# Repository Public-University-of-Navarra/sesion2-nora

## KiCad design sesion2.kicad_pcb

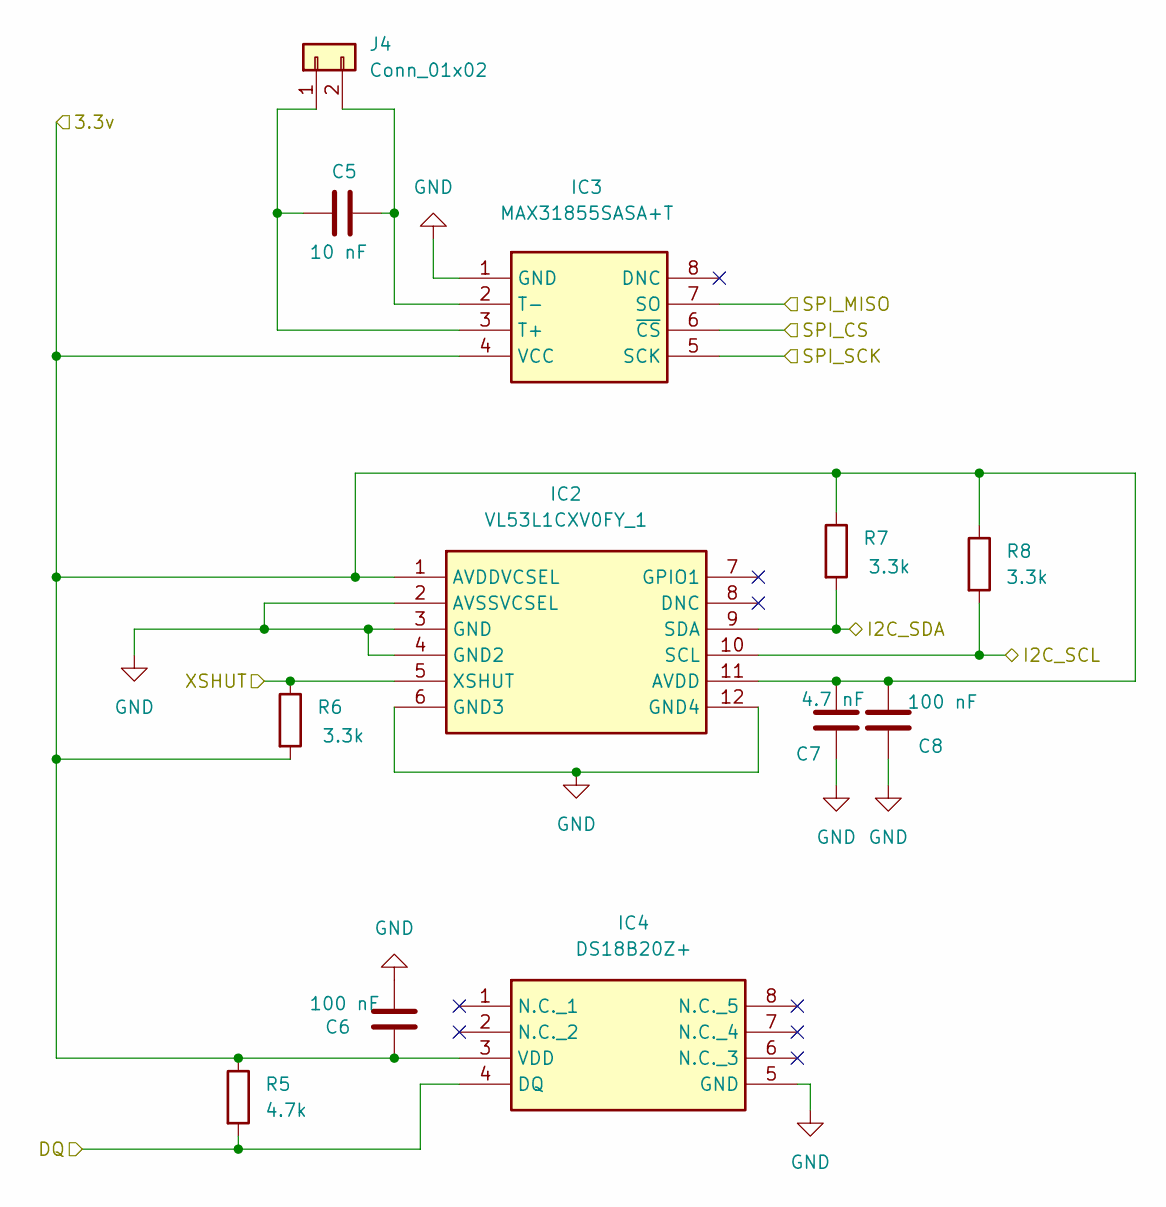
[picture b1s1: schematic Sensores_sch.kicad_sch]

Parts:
C5: 10 nF; C_0402_1005Metric
C6, C8: 100 nF; C_0402_1005Metric
C7: 4.7 nF; C_0402_1005Metric
IC2: VL53L1CXV0FY_1; VL53L1CXV0FY1; Mouser Part Number 511-VL53L1CXV0FY/1
IC3: MAX31855SASA+T; SOIC127P600X175-8N; Mouser Part Number 700-MAX31855SASA+T
IC4: DS18B20Z+; SOIC-8_3.9x4.9mm_P1.27mm; Mouser Part Number 700-DS18B20Z
J4: Conn_01x02; Altech_AK100_1x02_P5.00mm
R5: 4.7k; R_0402_1005Metric_Pad0.72x0.64mm_HandSolder
R6, R7, R8: 3.3k; R_0402_1005Metric_Pad0.72x0.64mm_HandSolder

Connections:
/Alimentacion/3.3v: C6.1, C7.2, C8.2, IC2.1 (AVDDVCSEL), IC2.11 (AVDD), IC3.4 (VCC), IC4.3 (VDD), R5.1, R6.2, R7.1, R8.1; also elsewhere on the board
/Microcontrolador/DQ: IC4.4 (DQ), R5.2; also elsewhere on the board
/Microcontrolador/I2C_SCL: IC2.10 (SCL), R8.2; also elsewhere on the board
/Microcontrolador/I2C_SDA: IC2.9 (SDA), R7.2; also elsewhere on the board
/Microcontrolador/SPI_CS: IC3.6 (~CS); also elsewhere on the board
/Microcontrolador/SPI_MISO: IC3.7 (SO); also elsewhere on the board
/Microcontrolador/SPI_SCK: IC3.5 (SCK); also elsewhere on the board
/Microcontrolador/XHUT: IC2.5 (XSHUT), R6.1; also elsewhere on the board
GND: C6.2, C7.1, C8.1, IC2.2 (AVSSVCSEL), IC2.3 (GND), IC2.4 (GND2), IC2.6 (GND3), IC2.12 (GND4), IC3.1 (GND), IC4.5 (GND); also elsewhere on the board
unnamed: C5.2, IC3.3 (T+), J4.1
unnamed: C5.1, IC3.2 (T-), J4.2

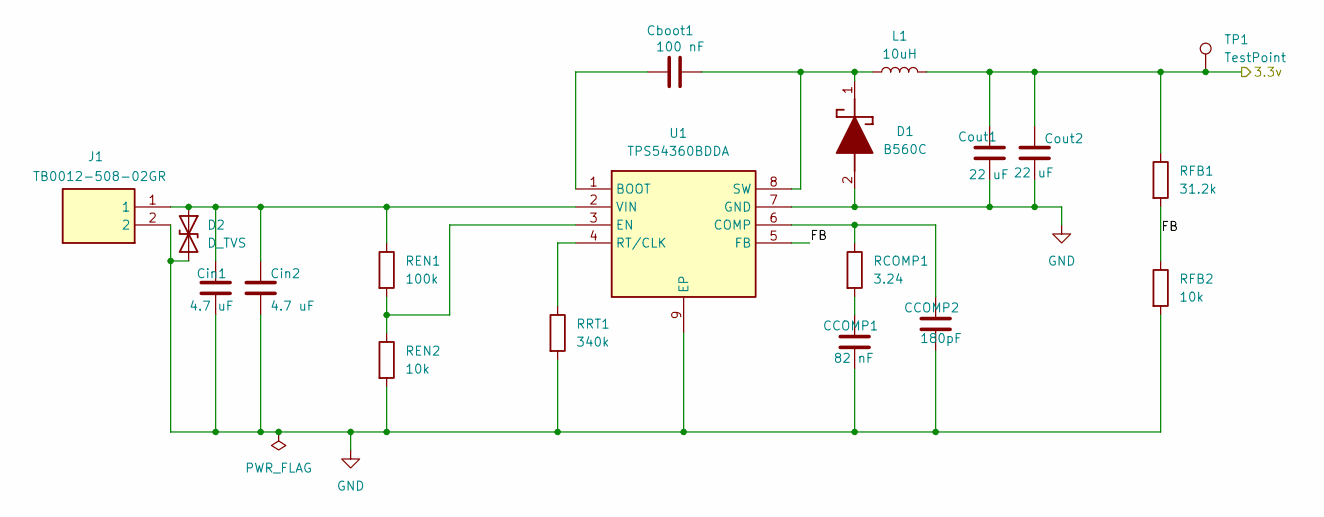
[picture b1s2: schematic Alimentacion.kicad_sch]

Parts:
CCOMP1: 82 nF; C_0402_1005Metric
CCOMP2: 180pF; C_0402_1005Metric
Cboot1: 100 nF; C_0402_1005Metric
Cin1, Cin2: 4.7 uF; C_0402_1005Metric
Cout1, Cout2: 22 uF; C_0402_1005Metric
D1: B560C; DIOM7959X250N; Mouser Part Number 621-560C
D2: D_TVS; D_SMA
J1: TB0012-508-02GR; Manufacturer_Part_Number TB0012-508-02GR
L1: 10uH; L_1206_3216Metric
RCOMP1: 3.24; R_0402_1005Metric_Pad0.72x0.64mm_HandSolder
REN1: 100k; R_0402_1005Metric_Pad0.72x0.64mm_HandSolder
REN2: 10k; R_0402_1005Metric_Pad0.72x0.64mm_HandSolder
RFB1: 31.2k; R_0402_1005Metric_Pad0.72x0.64mm_HandSolder
RFB2: 10k; R_0402_1005Metric_Pad0.72x0.64mm_HandSolder
RRT1: 340k; R_0402_1005Metric_Pad0.72x0.64mm_HandSolder
TP1: TestPoint; TestPoint_Pad_1.5x1.5mm
U1: TPS54360BDDA; SOIC127P600X170-9N; Mouser Part Number 595-TPS54360BDDA

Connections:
/Alimentacion/3.3v: Cout1.1, Cout2.1, L1.2, RFB1.1, TP1.1 (1_1); also elsewhere on the board
/Alimentacion/FB: RFB1.2, RFB2.1, U1.5 (FB)
GND: CCOMP1.2, CCOMP2.2, Cin1.2, Cin2.2, Cout1.2, Cout2.2, D1.2 (A), D2.2 (A2), J1.2, REN2.2, RFB2.2, RRT1.2, U1.7 (GND), U1.9 (EP); also elsewhere on the board
unnamed: CCOMP1.1, RCOMP1.2
unnamed: Cboot1.2, D1.1 (K), L1.1, U1.8 (SW)
unnamed: Cin1.1, Cin2.1, D2.1 (A1), J1.1, REN1.1, U1.2 (VIN)
unnamed: Cboot1.1, U1.1 (BOOT)
unnamed: CCOMP2.1, RCOMP1.1, U1.6 (COMP)
unnamed: REN1.2, REN2.1, U1.3 (EN)
unnamed: RRT1.1, U1.4 (RT/CLK)

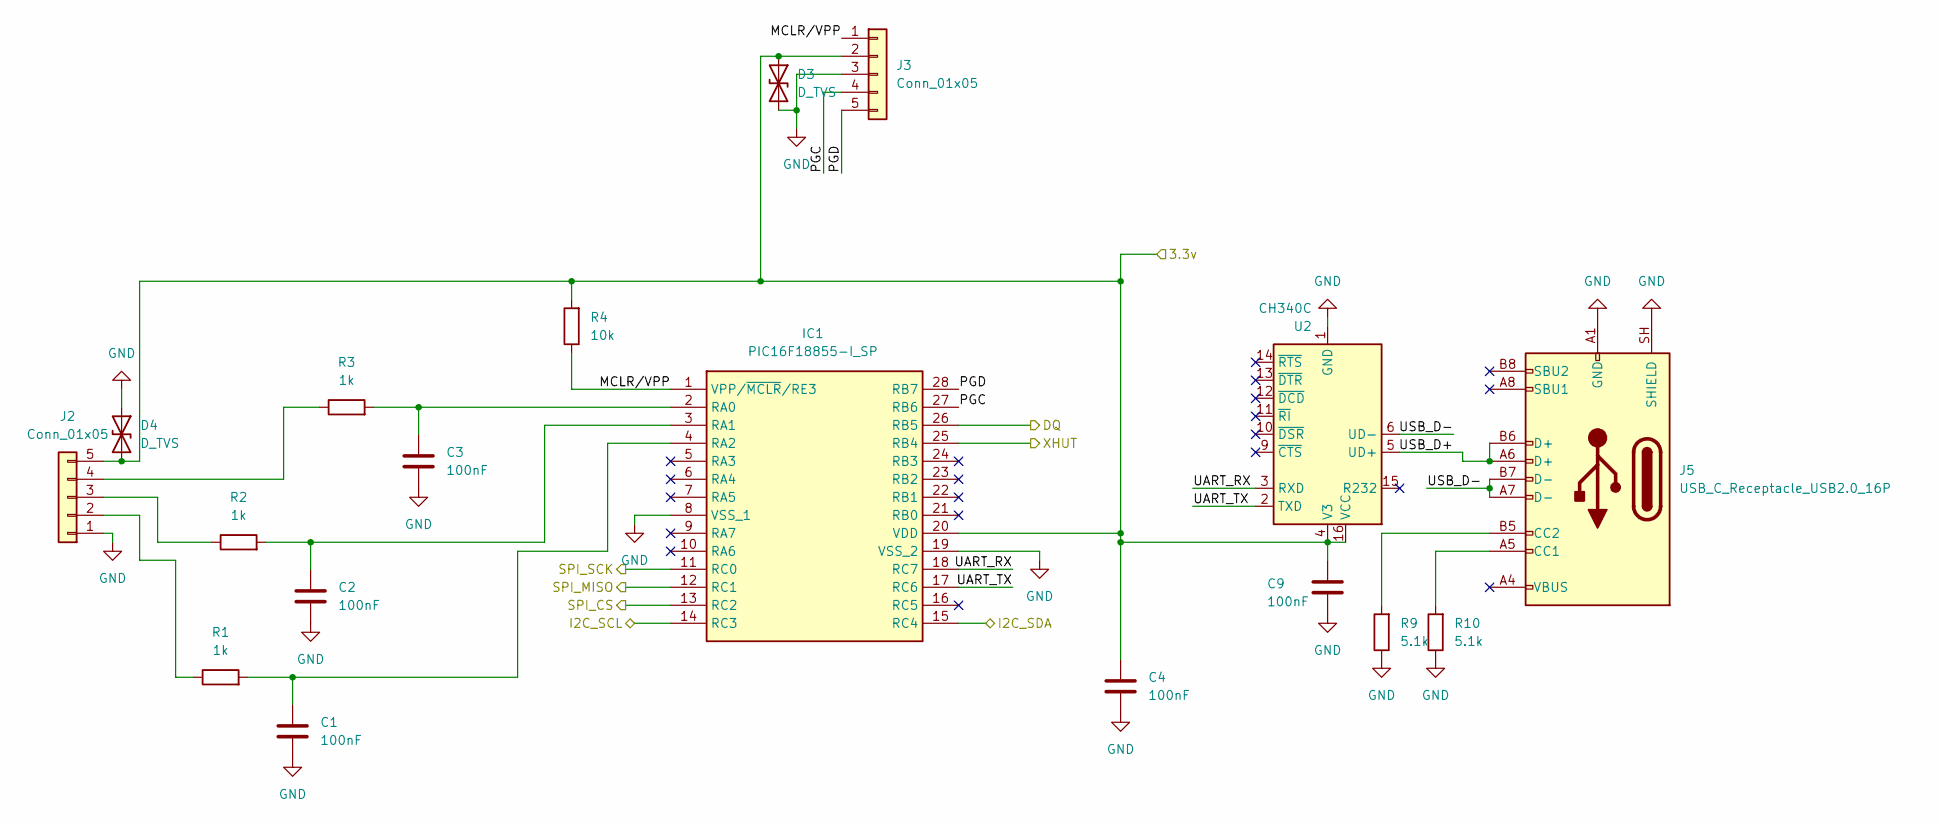
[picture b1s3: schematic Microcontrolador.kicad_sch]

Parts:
C1, C2, C3, C4, C9: 100nF; C_0402_1005Metric
D3: D_TVS; D_0402_1005Metric
D4: D_TVS; D_SMA
IC1: PIC16F18855-I_SP; DIP794W56P254L3486H508Q28N; Mouser Part Number 579-PIC16F18855-I/SP
J2, J3: Conn_01x05; PinHeader_1x05_P2.54mm_Vertical
J5: USB_C_Receptacle_USB2.0_16P; USB_C_Receptacle_GCT_USB4105-xx-A_16P_TopMnt_Horizontal
R1, R2, R3: 1k; R_0402_1005Metric_Pad0.72x0.64mm_HandSolder
R4: 10k; R_0402_1005Metric_Pad0.72x0.64mm_HandSolder
R9, R10: 5.1k; R_0402_1005Metric_Pad0.72x0.64mm_HandSolder
U2: CH340C; SOIC-16_3.9x9.9mm_P1.27mm

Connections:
/Alimentacion/3.3v: C4.1, C9.1, D3.1 (A1), D4.2 (A2), IC1.20 (VDD), J2.5, J3.2, R4.2, U2.4 (V3), U2.16 (VCC); also elsewhere on the board
/Microcontrolador/DQ: IC1.26 (RB5); also elsewhere on the board
/Microcontrolador/I2C_SCL: IC1.14 (RC3); also elsewhere on the board
/Microcontrolador/I2C_SDA: IC1.15 (RC4); also elsewhere on the board
/Microcontrolador/MCLR/VPP: IC1.1 (VPP/~MCLR/RE3), J3.1, R4.1
/Microcontrolador/PGC: IC1.27 (RB6), J3.4
/Microcontrolador/PGD: IC1.28 (RB7), J3.5
/Microcontrolador/SPI_CS: IC1.13 (RC2); also elsewhere on the board
/Microcontrolador/SPI_MISO: IC1.12 (RC1); also elsewhere on the board
/Microcontrolador/SPI_SCK: IC1.11 (RC0); also elsewhere on the board
/Microcontrolador/UART_RX: IC1.18 (RC7), U2.3 (RXD)
/Microcontrolador/UART_TX: IC1.17 (RC6), U2.2 (TXD)
/Microcontrolador/USB_D+: J5.A6 (D+), J5.B6 (D+), U2.5 (UD+)
/Microcontrolador/USB_D-: J5.A7 (D-), J5.B7 (D-), U2.6 (UD-)
/Microcontrolador/XHUT: IC1.25 (RB4); also elsewhere on the board
GND: C1.2, C2.2, C3.2, C4.2, C9.2, D3.2 (A2), D4.1 (A1), IC1.8 (VSS_1), IC1.19 (VSS_2), J2.1, J3.3, J5.A1 (GND), J5.A12 (GND), J5.B1 (GND), J5.B12 (GND), J5.SH (SHIELD), R9.1, R10.1, U2.1 (GND); also elsewhere on the board
unnamed: C3.1, IC1.2 (RA0), R3.2
unnamed: C2.1, IC1.3 (RA1), R2.2
unnamed: C1.1, IC1.4 (RA2), R1.2
unnamed: J2.2, R1.1
unnamed: J2.3, R2.1
unnamed: J2.4, R3.1
unnamed: J5.A5 (CC1), R10.2
unnamed: J5.B5 (CC2), R9.2

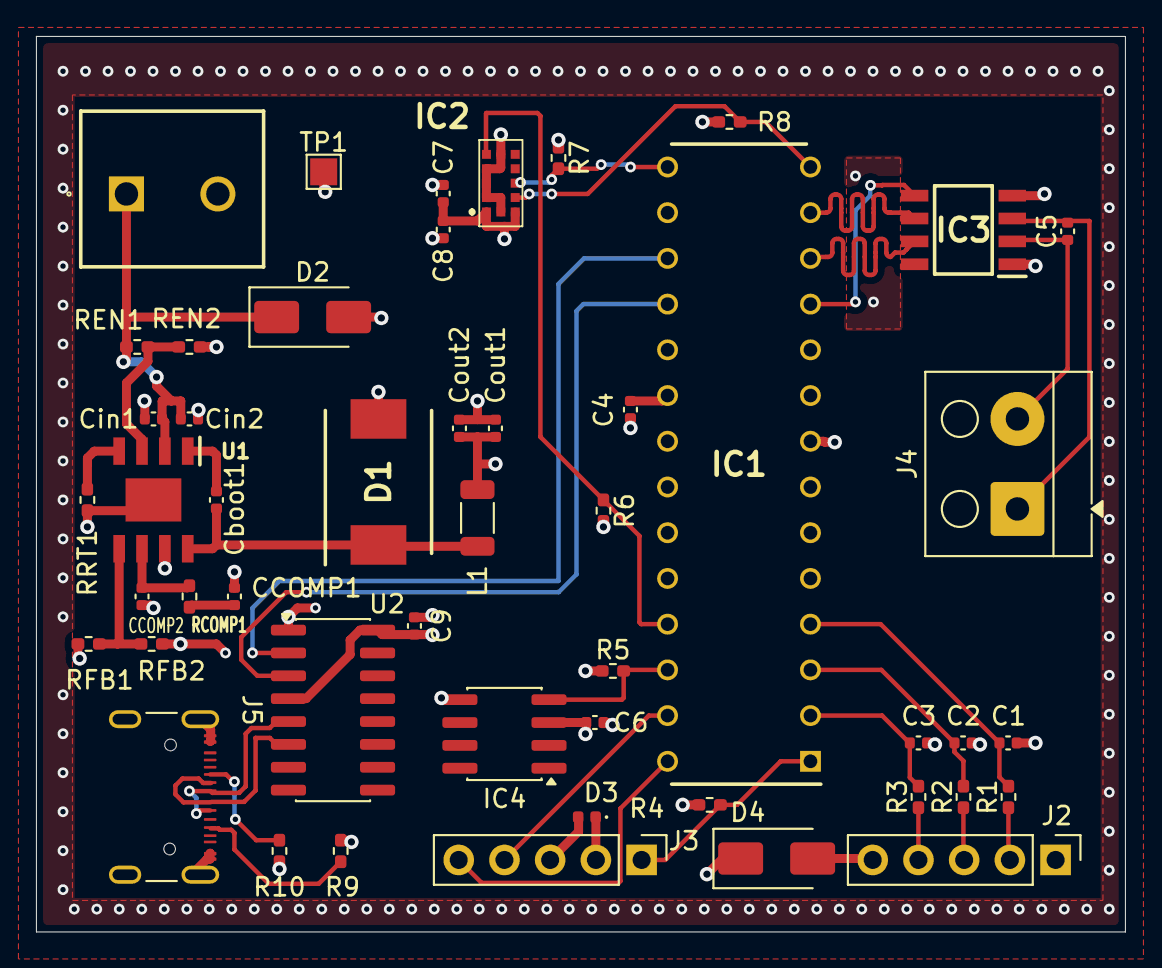
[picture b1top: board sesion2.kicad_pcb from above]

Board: 4 copper layers, 60.5 x 49.8 mm, 49 parts (0 on the bottom side), 34 nets.

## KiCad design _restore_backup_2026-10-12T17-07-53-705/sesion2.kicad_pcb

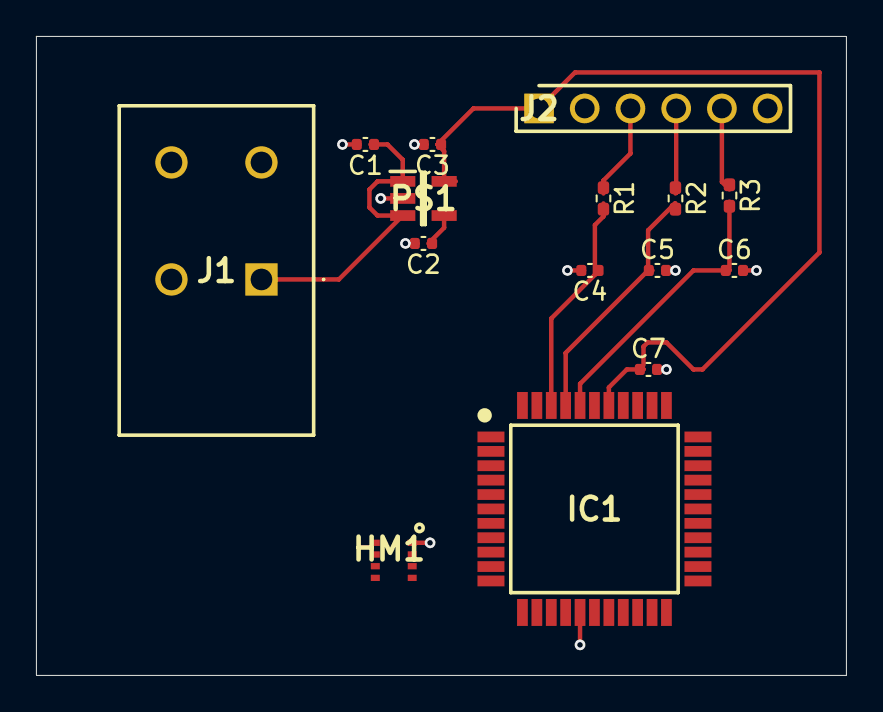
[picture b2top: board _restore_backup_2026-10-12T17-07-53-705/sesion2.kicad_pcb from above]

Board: 4 copper layers, 45.0 x 35.5 mm, 15 parts (0 on the bottom side), 14 nets.

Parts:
C1: 1uF; C_0402_1005Metric
C2: 0.01uF; C_0402_1005Metric
C3: 10uF; C_0402_1005Metric
C4, C5, C6, C7: 100nF; C_0402_1005Metric
HM1: BME280
IC1: AT89LS51-16AU; QFP80P1200X1200X120-44N
J1: 1366004
J2: 68000-106HLF; HDRV6W64P0X254_1X6_1524X254X839P
PS1: TAR5SB30_TE85L,F_; SOT95P275X140-5N
R1, R2, R3: 10k; R_0402_1005Metric_Pad0.72x0.64mm_HandSolder

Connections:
+9V: C1.1, J1.1, PS1.1 (VIN), PS1.3 (CONTROL)
/Microcontrolador/SPI_MISO: HM1.5 (SDO), IC1.2 ((MISO)_P1.6)
/Microcontrolador/SPI_MOSI: HM1.3 (SDI), IC1.1 ((MOSI)_P1.5)
/Microcontrolador/SPI_SCK: HM1.4 (SCK), IC1.3 ((SCK)_P1.7)
/Microcontrolador/vdd_mcu: C3.1, C7.1, HM1.6 (VDDIO), HM1.8 (VDD), IC1.38 (VCC), J2.1, PS1.5 (VOUT)
GND: C1.2, C2.2, C3.2, C4.2, C5.2, C6.2, C7.2, HM1.1 (GND_1), IC1.16 (GND_1), J1.2, J2.2, PS1.2 (GND)
unnamed: HM1.2 (CSB), IC1.44 (P1.4)
unnamed: C6.1, IC1.40 (P1.0), R3.2
unnamed: C5.1, IC1.41 (P1.1), R2.2
unnamed: C4.1, IC1.42 (P1.2), R1.2
unnamed: J2.3, R1.1
unnamed: J2.4, R2.1
unnamed: J2.5, R3.1
unnamed: C2.1, PS1.4 (NOISE)
